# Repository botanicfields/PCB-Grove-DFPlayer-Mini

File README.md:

# PCB-Grove-DFPlayer-Mini
a PCB to connect DFPlayer-Mini through Grove Connector

# DFPlayer-Mini 用 GROVE 接続基板
MP3 演奏モジュール DFPlayer-Mini を GROVE コネクタで簡単に接続するためのプリント基板です。フラッシュメモリ用 USB コネクタ、モニタースピーカー端子、ステレオ出力を備えます。押しボタンスイッチが 2 個あり、次の曲・前の曲の選択、長押しで音量増・減ができます。

販売委託（スイッチサイエンス）：  
https://www.switch-science.com/catalog/7310/

## 特徴
- GROVE ケーブルで M5 シリーズのポート (UART 設定) に直結できます。
- 3.5mm ミニジャックからステレオ音声を出力できます。
- ターミナルブロックにスピーカー（モノラル）を接続できます。
- USB-A コネクタからフラッシュメモリの楽曲を演奏できます。
- 押しボタンスイッチが 2 個あります。次の曲・前の曲、長押しで音量増・減ができます。

## ご注意
- DFPlayer-Mini（スイッチサイエンスSKU:4291）は付属しません。
- GROVE の電源は 5V 専用です。信号 (UART) は 3.3V です。
- USB-A コネクタは USB フラッシュメモリ専用です。
- 5V 信号ヘの接続を考慮し、TX, RX に保護抵抗 (1kΩ) を入れています。JP1(TX), JP2(RX) をハンダでショートすることでバイパスできます。TX は 3.3V で出力する方向ですので、保護抵抗は不要です。実験中の接続ミスなどを考慮して使用することもできます。
- ステレオ出力には、保護抵抗 (100Ω) を入れています。出力レベルが不足する場合、JP3(R), JP4(L) をハンダでショートすることでバイパスできます。
- プリント基板単体の完成品です。ケースや足はありません。部品の足が剥き出しのため、絶縁材や四隅の穴にスペーサを取り付けるなどして、負傷、静電気破壊、机の傷などを防止ください。

## サンプルプログラム

DF-029.ino は、M5Atom 用です。M5Atom の GROVE ポートに DFPlayer-Mini を接続します。5 秒ごとに次の曲を演奏します。M5Atom のボタンを押すと、microSD・USB フラッシュの選択が切り替わります。

## 内容物

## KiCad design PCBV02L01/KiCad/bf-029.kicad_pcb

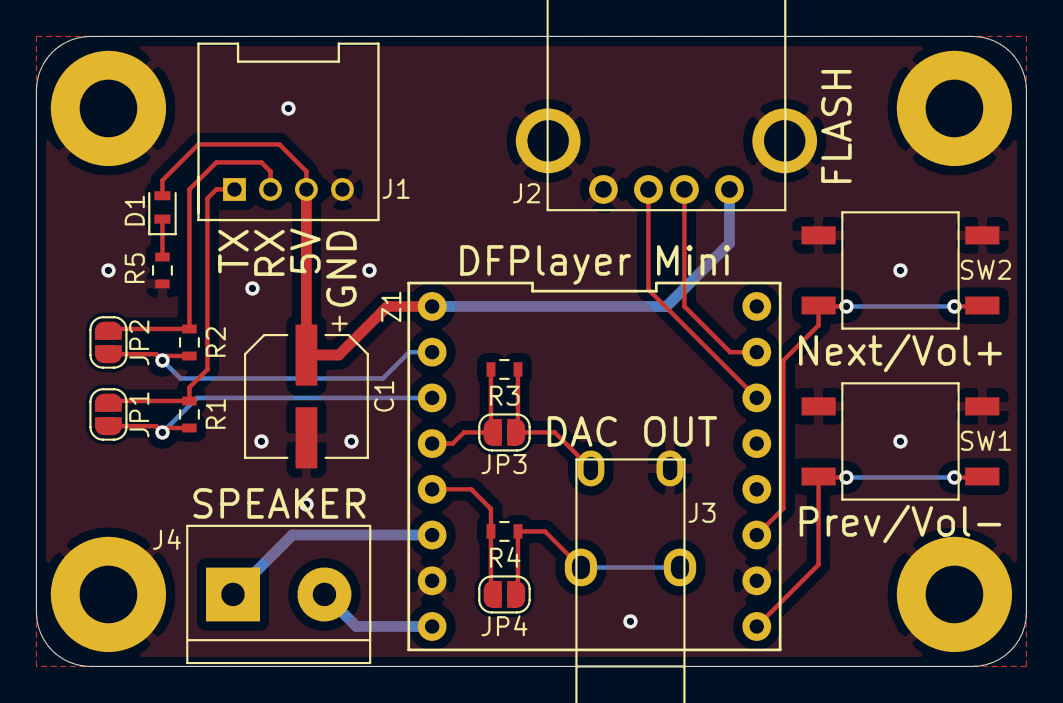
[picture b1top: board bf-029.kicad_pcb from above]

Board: 2 copper layers, 55.0 x 35.0 mm, 18 parts (0 on the bottom side), 17 nets.

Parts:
C1: 100u; BF@CP_Elec_6.3x5.3
D1: LED; BF@LED_0603_1608Metric
J1: SERIAL; HW4-2.0-90D
J2: USB FLASH; BF@USB-A-5075AR
J3: DAC OUT; BF@MJ8435
J4: SPEAKER; BF@TerminalBlock_2_P5.08mm_d1.3mm
JP1: BY1; SolderJumper-2_P1.3mm_Open_RoundedPad1.0x1.5mm
JP2: BY2; SolderJumper-2_P1.3mm_Open_RoundedPad1.0x1.5mm
JP3: BY3; SolderJumper-2_P1.3mm_Open_RoundedPad1.0x1.5mm
JP4: BY4; SolderJumper-2_P1.3mm_Open_RoundedPad1.0x1.5mm
R1, R2: 1k; BF@R_0603_1608Metric
R3, R4: 100; BF@R_0603_1608Metric
R5: 3.3k; BF@R_0603_1608Metric
SW1: Prev/Vol-; BF@K2-6639SP
SW2: Next/Vol+; BF@K2-6639SP
Z1: DFPlayer-Mini; BF@MP3-TF-16P

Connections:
/RX: J1.2, JP2.1, R2.2
/TX: J1.1, JP1.1, R1.2
GND: C1.2, J1.4, J2.4, J2.5, J3.S, R5.1, SW1.1, SW2.1, Z1.7, Z1.10
unnamed: C1.1, D1.2, J1.3, J2.1, Z1.1
unnamed: D1.1, R5.2
unnamed: J2.2, Z1.15
unnamed: J2.3, Z1.14
unnamed: J3.R, JP3.1, R3.2
unnamed: J3.T, JP4.1, R4.2
unnamed: J4.1, Z1.6
unnamed: J4.2, Z1.8
unnamed: JP1.2, R1.1, Z1.3
unnamed: JP2.2, R2.1, Z1.2
unnamed: JP3.2, R3.1, Z1.4
unnamed: JP4.2, R4.1, Z1.5
unnamed: SW1.2, Z1.9
unnamed: SW2.2, Z1.11

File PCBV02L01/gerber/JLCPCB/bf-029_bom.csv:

Comment,Designator,Footprint,LCSC
100u,C1,bf:BF@CP_Elec_6.3x5.3,C134749
LED,D1,bf:BF@LED_0603_1608Metric,C72041
SERIAL,J1,OPL_Connector:HW4-2.0-90D,
USB FLASH,J2,bf:BF@USB-A-5075AR,
DAC OUT,J3,bf:BF@MJ8435,
SPEAKER,J4,bf:BF@TerminalBlock_2_P5.08mm_d1.3mm,
BY1,JP1,Jumper:SolderJumper-2_P1.3mm_Open_RoundedPad1.0x1.5mm,
BY2,JP2,Jumper:SolderJumper-2_P1.3mm_Open_RoundedPad1.0x1.5mm,
BY3,JP3,Jumper:SolderJumper-2_P1.3mm_Open_RoundedPad1.0x1.5mm,
BY4,JP4,Jumper:SolderJumper-2_P1.3mm_Open_RoundedPad1.0x1.5mm,
1k,"R1,R2",bf:BF@R_0603_1608Metric,C21190
100,"R3,R4",bf:BF@R_0603_1608Metric,C22775
3.3k,R5,bf:BF@R_0603_1608Metric,C22978
Prev/Vol-,SW1,bf:BF@K2-6639SP,C83206
Next/Vol+,SW2,bf:BF@K2-6639SP,C83206
DFPlayer-Mini,Z1,bf:BF@MP3-TF-16P,

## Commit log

2021-06-06 V02L01
    PCB, Library, Footprint
2021-06-27 image
    add images
2021-06-29 Create bf-029_doc.pdf
    add DOC
2021-07-06 image
2021-12-18 Update BF-029.ino
    add unsigned to "int last_ms"

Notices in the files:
PCBV02L01/KiCad/bf-029.kicad_pcb:
Copyright 2021 BotanicFields, Inc.
